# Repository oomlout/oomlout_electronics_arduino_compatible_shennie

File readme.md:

# oomlout_oomp_electronic_breakout_board_mcu_atmega328_shennie

A repository designed to recreate the design files for the ubiquotously available arduino nano clone from aliexpress.

oomp_key: oomp_electronic_breakout_board_mcu_atmega328_shennie
oomp_part: https://github.com/oomlout/oomlout_oomp_part_src/tree/main/parts/electronic_breakout_board_mcu_atmega328_shennie/working

# parts

* u1    atmega              oomp_electronic_ic_tqfp_32_mcu_atmega328_microchip_atmega328p_aur
* x1    crystal             oomp_electronic_crystal_3215_16_mega_hertz
* s1    button              oomp_electronic_button_3_5_mm_x_6_mm_x_2_5_mm_surface_mount
* d1    led rx              oomp_electronic_led_0603
* d2    led tx              oomp_electronic_led_0603
* d3    led pow             oomp_electronic_led_0603
* d4    led l               oomp_electronic_led_0603
* r1                        oomp_electronic_resistor_0603_1000_ohm
* r1                        oomp_electronic_resistor_0603_1000_ohm
* r1                        oomp_electronic_resistor_0603_1000_ohm
* r1                        oomp_electronic_resistor_0603_1000_ohm

bottom
* u2    serial chip         oomp_electronic_ic_sop_16_converter_usb_to_serial_converter_wch_ch340c
* x2    crystal             oomp_electronic_crystal_3215_12_mega_hertz
* u3    linear regulator    oomp_electronic_pmic_sot_223_linear_1117_3_3v
* c1    4.7 uf capacitor    electronic_capacitor_3216_avx_a_tantalum_4_7_micro_farad_16_volt
* c2    4.7 uf capacitor    electronic_capacitor_3216_avx_a_tantalum_4_7_micro_farad_16_volt

# modules

*

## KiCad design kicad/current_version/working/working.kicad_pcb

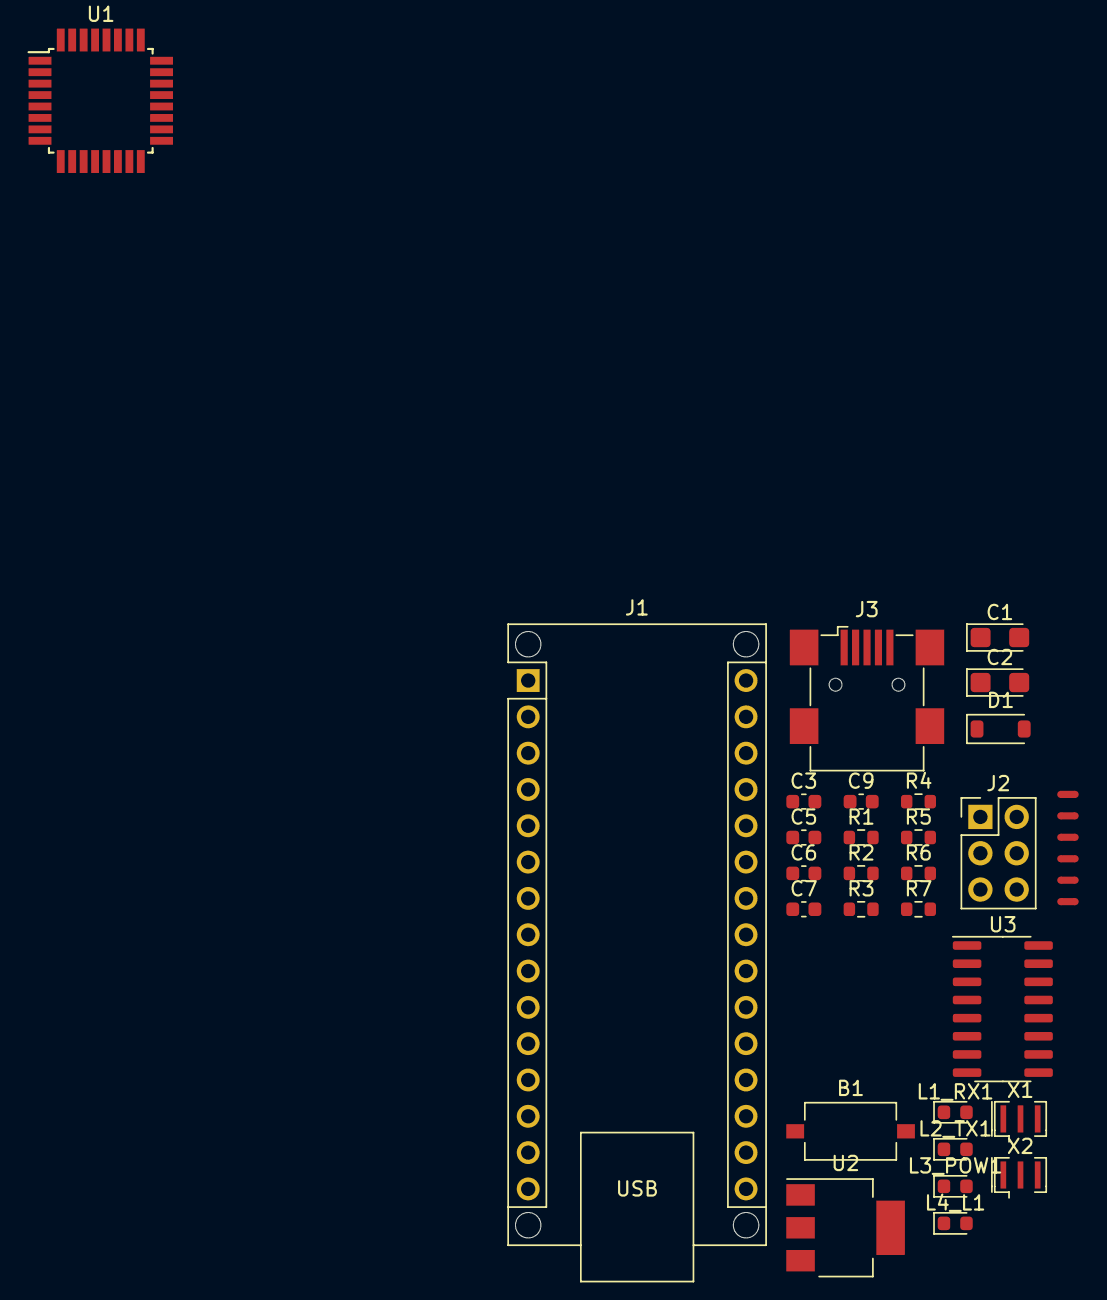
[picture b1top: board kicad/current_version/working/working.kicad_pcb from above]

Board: 2 copper layers, 34 parts (0 on the bottom side), 39 nets, no tracks yet.

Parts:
1111, 11111: nt2; nt2_electronic_nettie_2_nets_smd
B1: b3560s; b3560s_electronic_button_3_5_mm_x_6_mm_x_2_5_mm_surface_mou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
C1, C2: catuf4d716v; catuf4d716v_electronic_capacitor_3216_avx_a_tantalum_4_7_mi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
C3: c6nf10; c6nf10_electronic_capacitor_0603_10_nano_farad
C5, C6, C7, C9: c6nf100; c6nf100_electronic_capacitor_0603_100_nano_farad
D1: dssod123pmb2; dssod123pmb2_electronic_diode_schottky_sod_123_package_mark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
J1: bbat328; bbat328_electronic_breakout_board_mcu_atmega328_shennie
J2: hi12x3p; hi12x3p_electronic_header_2d54_mm_dual_row_2x3_dual_row_6_p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
J3: scumnsmo; scumnsmo_electronic_socket_usb_mini_surface_mount_only
L1_RX1, L2_TX1, L3_POW1, L4_L1: l6r; l6r_electronic_led_0603_red
R1, R2, R3, R4, R5, R6, R7: r6o102; r6o102_electronic_resistor_0603_1000_ohm
U1: itq32at328; itq32at328_electronic_ic_tqfp_32_mcu_atmega328_microchip_at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
U2: pms22311171d5v; pms22311171d5v_electronic_pmic_sot_223_linear_1117_1_5_volt
U3: isp16ch340g; isp16ch340g_electronic_ic_sop_16_converter_usb_to_serial_co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
X1: xcr3213mhz16; xcr3213mhz16_electronic_ceramic_resonator_3213_3_pin_ground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
X2: xcr3213mhz12; xcr3213mhz12_electronic_ceramic_resonator_3213_3_pin_ground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
nt1, nt2, nt5, nt6: nt2; nt2_electronic_nettie_2_nets_smd

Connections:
+5V: B1.2, C1.2, C2.1, C2.2, C3.2, C5.1, C6.1, C6.2, C7.2, C9.1, C9.2, D1.1 (K), J1.4 (GND), J1.27 (+5V), J1.29 (GND), J2.2, J2.6, J3.5 (GND), J3.6 (Shield), L1_RX1.2 (A), L2_TX1.2 (A), L3_POW1.1 (K), L4_L1.1 (K), R3.2, R7.2, U1.3 (GND), U1.4 (VCC), U1.5 (GND), U1.6 (VCC), U1.18 (AVCC), U1.21 (GND), U2.1 (GND), U2.2 (VO), U3.1 (GND), U3.16 (VCC), X1.2, X2.2
+12V: C1.1, C7.1, J1.30 (VIN), U2.3 (VI)
/adc4: J1.23 (A4), U1.27 (PC4)
/adc5: J1.24 (A5), U1.28 (PC5)
/adc6: J1.25 (A6), U1.19 (ADC6)
/adc7: J1.26 (A7), U1.22 (ADC7)
/aref: J1.18 (AREF), U1.20 (AREF)
/dtr: R7.1, U3.13 (~DTR)
/miso: J1.15 (D12), U1.16 (PB4)
/mosi: J1.14 (D11), J2.4, U1.15 (PB3)
/pb0: J1.11 (D8), U1.12 (PB0)
/pb1: J1.12 (D9), U1.13 (PB1)
/pb2: J1.13 (D10), U1.14 (PB2)
/pb5: J1.16 (D13), U1.17 (PB5)
/pc0: J1.19 (A0), U1.23 (PC0)
/pc1: J1.20 (A1), U1.24 (PC1)
/pc2: J1.21 (A2), U1.25 (PC2)
/pc3: J1.22 (A3), U1.26 (PC3)
/pc6: B1.1, C5.2, J1.3 (~RESET), J1.28 (~RESET), U1.29 (~RESET/PC6)
/pd0: 1111.2, J1.2 (D0/RX), R1.2, U1.30 (PD0), nt2.1, nt6.1, nt6.2
/pd1: 11111.2, J1.1 (D1/TX), R2.2, U1.31 (PD1), nt1.1, nt5.1, nt5.2
/pd2: J1.5 (D2), U1.32 (PD2)
/pd3: J1.6 (D3), U1.1 (PD3)
/pd4: J1.7 (D4), U1.2 (PD4)
/pd5: J1.8 (D5), U1.9 (PD5)
/pd6: J1.9 (D6), U1.10 (PD6)
/pd7: J1.10 (D7), U1.11 (PD7)
/rx_ch340: 11111.1, R6.2, nt1.2
/tx_ch340: 1111.1, R5.2, nt2.2
/usb_negative: J3.2 (D-), U3.6 (UD-)
/usb_plus: J3.3 (D+), U3.5 (UD+)
unnamed: D1.2 (A), J3.1 (VBUS)
unnamed: L1_RX1.1 (K), R1.1
unnamed: L2_TX1.1 (K), R2.1
unnamed: L3_POW1.2 (A), R3.1
unnamed: L4_L1.2 (A), R4.1
unnamed: R6.1, U3.3 (RXD)
unnamed: R5.1, U3.2 (TXD)
unnamed: C3.1, U3.4 (V3)

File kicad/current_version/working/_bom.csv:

"Id";"Designator";"Footprint";"Quantity";"Designation";"Supplier and ref";
1;"L3_POW1,L2_TX1,L4_L1,L1_RX1";"l6r_electronic_led_0603_red";4;"l6r";;;
2;"J3";"scumnsmo_electronic_socket_usb_mini_surface_mount_only";1;"scumnsmo";;;
3;"X1";"xcr3213mhz16_electronic_ceramic_resonator_3213_3_pin_ground_pin_2_16_mega_hertz";1;"xcr3213mhz16";;;
4;"R3,R4,R1,R2,R7,R5,R6";"r6o102_electronic_resistor_0603_1000_ohm";7;"r6o102";;;
5;"J2";"hi12x3p_electronic_header_2d54_mm_dual_row_2x3_dual_row_6_pin";1;"hi12x3p";;;
6;"B1";"b3560s_electronic_button_3_5_mm_x_6_mm_x_2_5_mm_surface_mount";1;"b3560s";;;
7;"U1";"itq32at328_electronic_ic_tqfp_32_mcu_atmega328_microchip_atmega328p_aur";1;"itq32at328";;;
8;"J1";"bbat328_electronic_breakout_board_mcu_atmega328_shennie";1;"bbat328";;;
9;"C1,C2";"catuf4d716v_electronic_capacitor_3216_avx_a_tantalum_4_7_micro_farad_16_volt";2;"catuf4d716v";;;
10;"U3";"isp16ch340g_electronic_ic_sop_16_converter_usb_to_serial_converter_wch_ch340g";1;"isp16ch340g";;;
11;"U2";"pms22311171d5v_electronic_pmic_sot_223_linear_1117_1_5_volt";1;"pms22311171d5v";;;
12;"C6,C7,C4,C5";"c6nf100_electronic_capacitor_0603_100_nano_farad";4;"c6nf100";;;
13;"D1";"dssod123pmb2_electronic_diode_schottky_sod_123_package_marking_b2_mbr0520";1;"dssod123pmb2";;;
14;"X2";"xcr3213mhz12_electronic_ceramic_resonator_3213_3_pin_ground_pin_2_12_mega_hertz";1;"xcr3213mhz12";;;
15;"C3";"c6nf10_electronic_capacitor_0603_10_nano_farad";1;"c6nf10";;;

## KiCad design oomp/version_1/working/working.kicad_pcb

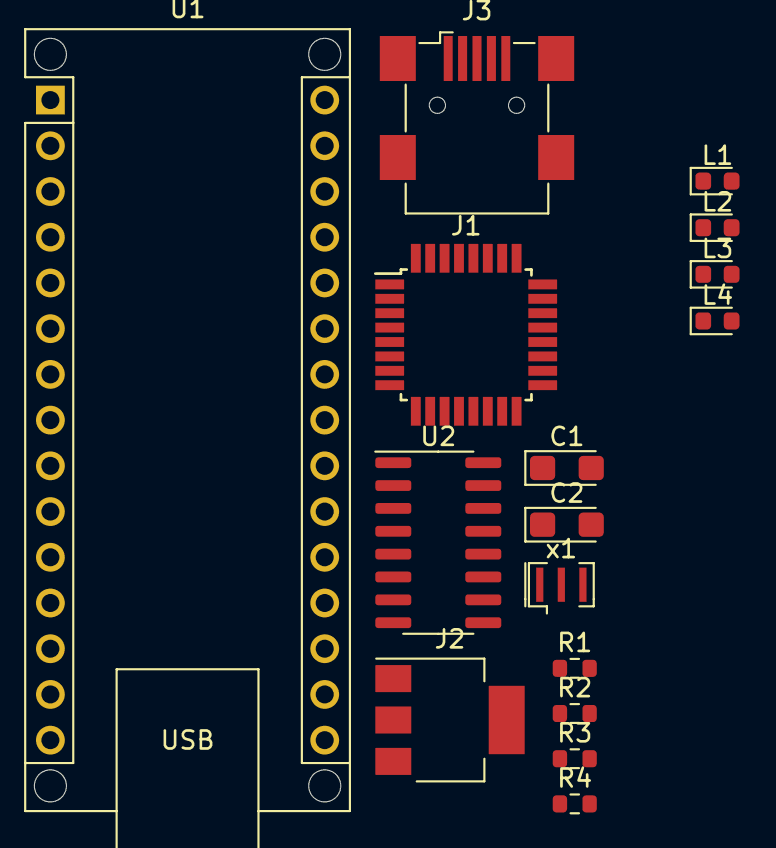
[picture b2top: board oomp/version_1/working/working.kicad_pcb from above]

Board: 2 copper layers, 16 parts (0 on the bottom side), 36 nets, no tracks yet.

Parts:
C1, C2: catuf4d7; catuf4d7_electronic_capacitor_3216_avx_a_tantalum_4_7_micro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
J1: itq32at328_electronic_ic_tqfp_32_mcu_atmega328_mi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; itq32at328_electronic_ic_tqfp_32_mcu_atmega328_microchip_at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
J2: pms2231117; pms2231117_electronic_pmic_sot_223_linear_1117_5v
J3: scumnsmo; scumnsmo_electronic_socket_usb_mini_surface_mount_only
L1, L2, L3, L4: l6r; l6r_electronic_led_0603_red
R1, R2, R3, R4: r6o102; r6o102_electronic_resistor_0603_1000_ohm
U1: bbat328; bbat328_electronic_breakout_board_mcu_atmega328_shennie
U2: isp16ch340c; isp16ch340c_electronic_ic_sop_16_converter_usb_to_serial_co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
x1: x3213mhz16; x3213mhz16_electronic_crystal_3213_3_pin_ground_pin_2_16_me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

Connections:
+3V3: C2.1, J2.2 (VO), U1.17 (3V3)
+5V: J1.4 (VCC), J1.6 (VCC), J1.18 (AVCC), J3.1 (VBUS), U1.27 (+5V), U2.16 (VCC)
+12V: C1.1, J2.3 (VI), U1.30 (VIN)
/adc6: J1.19 (ADC6), U1.25 (A6)
/adc7: J1.22 (ADC7), U1.26 (A7)
/aref: J1.20 (AREF), U1.18 (AREF)
/pb0: J1.12 (PB0), U1.11 (D8)
/pb1: J1.13 (PB1), U1.12 (D9)
/pb2: J1.14 (PB2), U1.13 (D10)
/pb3: J1.15 (PB3), U1.14 (D11)
/pb4: J1.16 (PB4), U1.15 (D12)
/pb5: J1.17 (PB5), U1.16 (D13)
/pb6: J1.7 (XTAL1/PB6), x1.1
/pb7: J1.8 (XTAL2/PB7), x1.3
/pc0: J1.23 (PC0), U1.19 (A0)
/pc1: J1.24 (PC1), U1.20 (A1)
/pc2: J1.25 (PC2), U1.21 (A2)
/pc3: J1.26 (PC3), U1.22 (A3)
/pc4: J1.27 (PC4), U1.23 (A4)
/pc5: J1.28 (PC5), U1.24 (A5)
/pc6: J1.29 (~RESET/PC6), U1.3 (~RESET), U1.28 (~RESET)
/pd0: J1.30 (PD0), U1.2 (D0/RX), U2.2 (TXD)
/pd1: J1.31 (PD1), U1.1 (D1/TX), U2.3 (RXD)
/pd2: J1.32 (PD2), U1.5 (D2)
/pd3: J1.1 (PD3), U1.6 (D3)
/pd4: J1.2 (PD4), U1.7 (D4)
/pd5: J1.9 (PD5), U1.8 (D5)
/pd6: J1.10 (PD6), U1.9 (D6)
/pd7: J1.11 (PD7), U1.10 (D7)
/usb_negative: J3.2 (D-), U2.6 (UD-)
/usb_plus: J3.3 (D+), U2.5 (UD+)
GND: C1.2, C2.2, J1.3 (GND), J1.5 (GND), J1.21 (GND), J2.1 (GND), J3.5 (GND), L1.1 (K), L2.1 (K), L3.1 (K), L4.1 (K), U1.4 (GND), U1.29 (GND), U2.1 (GND), x1.2
unnamed: L1.2 (A), R1.1
unnamed: L2.2 (A), R2.1
unnamed: L3.2 (A), R3.1
unnamed: L4.2 (A), R4.1

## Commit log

2023-08-08 getting started.
2023-08-20 first run of documenting
2023-08-20 changed version
2023-08-20 updated gitignore
2023-08-24 added pcb images
2023-08-24 workings
2023-08-26 working
2023-08-26 changed old_attempt name
2023-08-26 a bit
2023-08-26 autogen full run
2023-08-28 started routing backside needs swapping over
2023-08-28 full gen
2023-08-28 fixing gitignore
2023-09-03 fixed backups being saved
